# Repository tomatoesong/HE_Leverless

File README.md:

# HE_Leverless

# 🎮 Hall Effect Fighting Game Controller  

A custom-built **fighting game controller** featuring **Hall effect sensors** based on ESP32-S3 for ultra-durable, low latency performance. Designed for competitive play, modularity, and long-term reliability.  

---

## ✨ Features  

- 🕹 **Hall Effect Sensors** – no wear and tear from metal contact based switches 
- 🔧 **Modular Design** – easily replace buttons, just pull out an switch and snap in a new one
- ⚡ **Low Latency** – optimized input response at over 2000Hz polling with fully customizable actuation points for every switch!
- 🌐 **Web UI** - web based UI for customizing board on the go from anywhere without the need for connecting to a PC
- 💻 **Open Source Firmware** – customizable and community-driven  
- 🎨 **Custom Build** – unique layout and aesthetics  

---

## Custom PCB Layout  

| Front View |
|------------|
|  |

Created Using KiCad and custom library and footprints!

### ✅ PCB Features
- Digital and Analog ground plane seperation
- Low count BOM
- One sided for easy of assembly on hot plate or oven!

---

## Web-Based UI 

| Startup View | Selection | Save with Ease |
|------------|------------|------------|
|  |  |  |

Fully integrated and interactable WEB UI from an embedded board

### ✅ WEB-UI Features
- Hosts it's own Wifi you connect to
- Access the configurator from any browser at 192.168.10.1
- Individually switch values can be set with intuitive UI indicating what button you are adjusting
- 5 MICRON steps of adjustment for HIGH precision customization

---

## CAD Model  
<!--
| Front View | Inside View | 
|------------|-------------|
|  |  |

*(Replace the image paths with your actual files, e.g., `/assets/controller-front.png`)*  
-->
| Front View |
|------------|
|  |

| WireFrame View |
|------------|
|  |

Designed in Fusion360 with all components modeled for accuracy. 

---

## 🚀 Getting Started  

1. Clone this repo:  
   ```bash
   git clone https://github.com/your-username/your-controller-repo.git

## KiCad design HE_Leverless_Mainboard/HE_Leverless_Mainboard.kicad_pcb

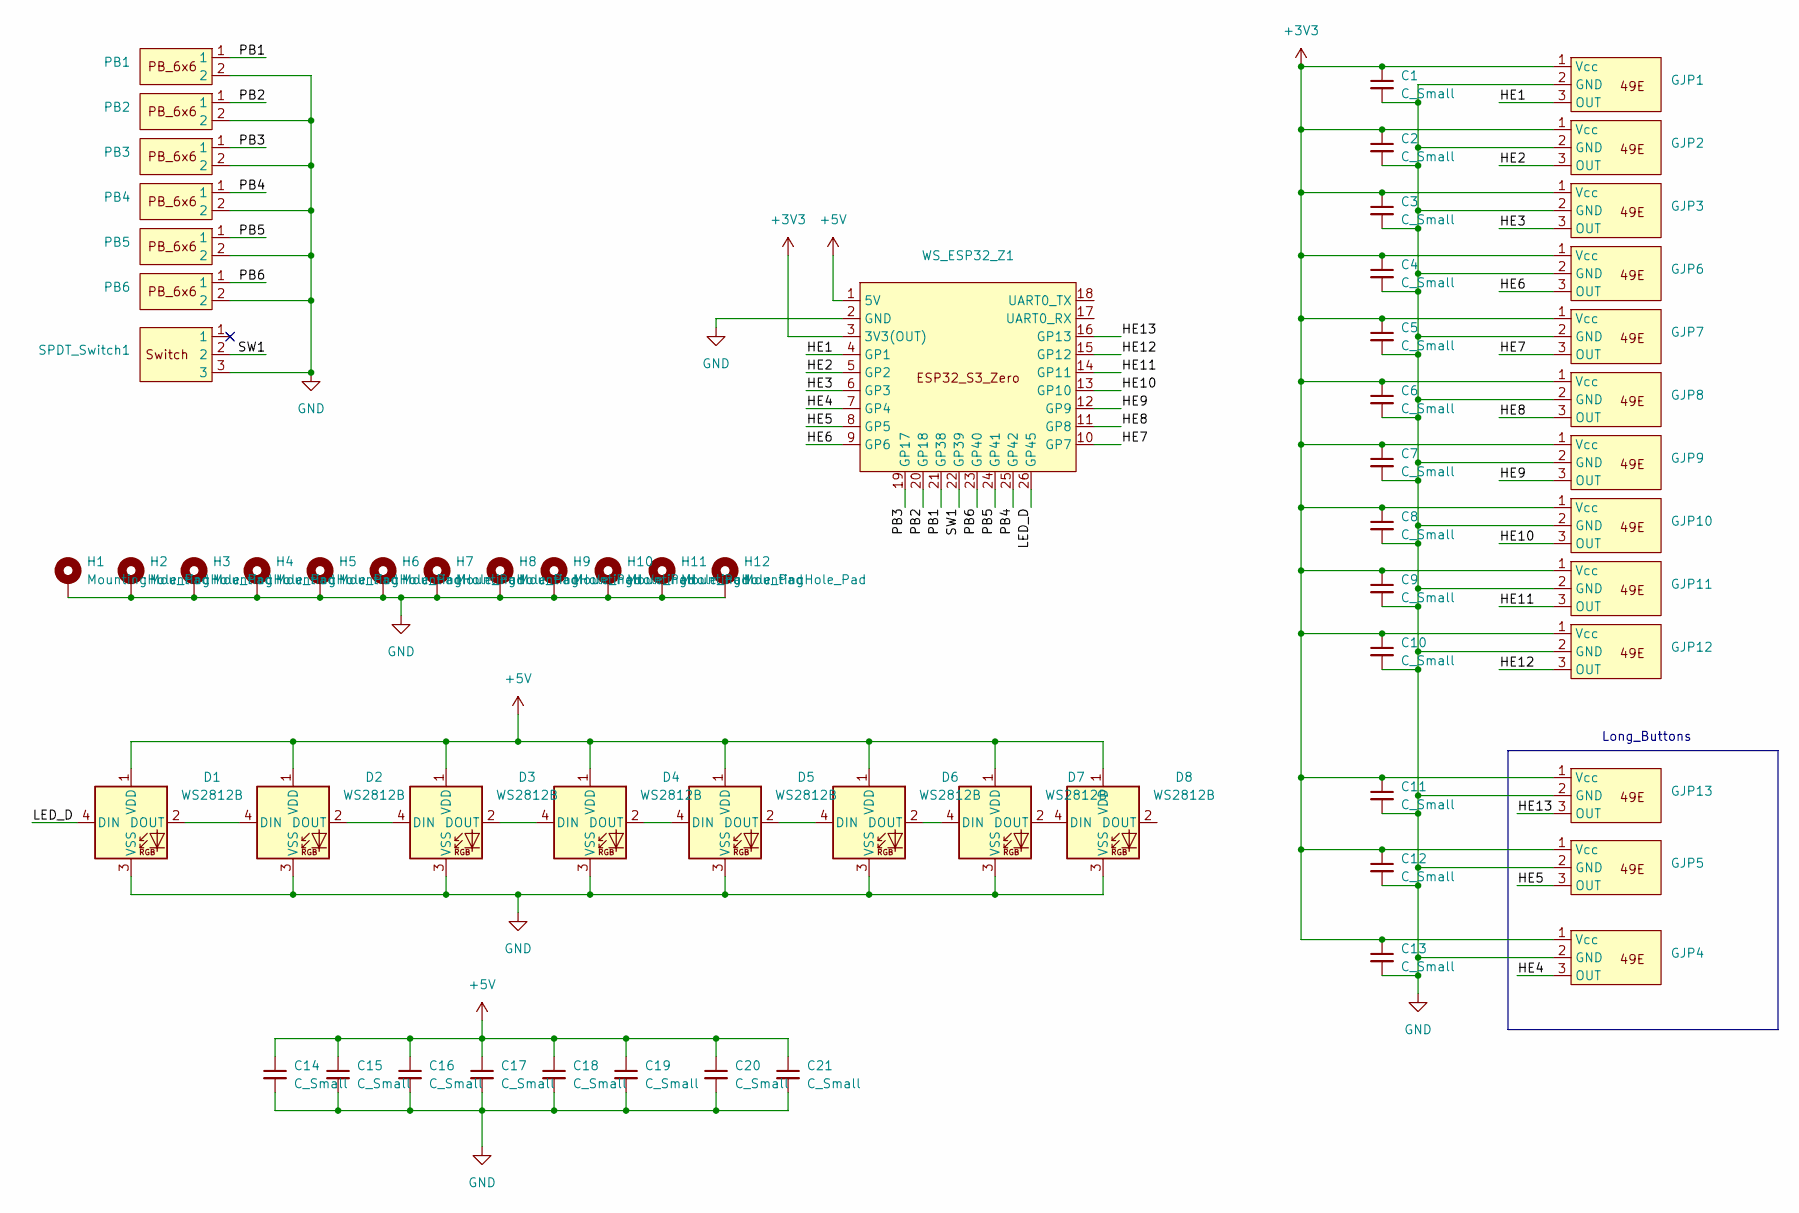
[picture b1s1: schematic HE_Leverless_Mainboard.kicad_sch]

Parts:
C1, C2, C3, C4, C5, C6, C7, C8, C9, C10, C11, C12, C13, C14, C15, C16, C17, C18, C19, C20, C21: C_Small; C_0805_2012Metric
D1, D2, D3, D4, D5, D6, D7, D8: WS2812B; LED_WS2812B_PLCC4_5.0x5.0mm_P3.2mm
GJP1, GJP2, GJP3, GJP6, GJP7, GJP8, GJP9, GJP10, GJP11, GJP12: Gateron_Jade_Pro
GJP4: Gateron_Jade_Pro_3
GJP5, GJP13: Gateron_Jade_Pro_2
H1, H2, H3, H4, H5, H6, H7, H8, H9, H10, H11, H12: MountingHole_Pad; MountingHole_3.2mm_M3_Pad
PB1, PB2, PB3, PB4, PB5, PB6: 6x6_PushButton
SPDT_Switch1: 1P2T_SPDT_Switch
WS_ESP32_Z1: WS_ESP32_S3_Zero

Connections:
+3V3: C1.1, C2.1, C3.1, C4.1, C5.1, C6.1, C7.1, C8.1, C9.1, C10.1, C11.1, C12.1, C13.1, GJP1.1 (Vcc), GJP2.1 (Vcc), GJP3.1 (Vcc), GJP4.1 (Vcc), GJP5.1 (Vcc), GJP6.1 (Vcc), GJP7.1 (Vcc), GJP8.1 (Vcc), GJP9.1 (Vcc), GJP10.1 (Vcc), GJP11.1 (Vcc), GJP12.1 (Vcc), GJP13.1 (Vcc), WS_ESP32_Z1.3 (3V3(OUT))
+5V: C14.1, C15.1, C16.1, C17.1, C18.1, C19.1, C20.1, C21.1, D1.1 (VDD), D2.1 (VDD), D3.1 (VDD), D4.1 (VDD), D5.1 (VDD), D6.1 (VDD), D7.1 (VDD), D8.1 (VDD), WS_ESP32_Z1.1 (5V)
/HE1: GJP1.3 (OUT), WS_ESP32_Z1.4 (GP1)
/HE2: GJP2.3 (OUT), WS_ESP32_Z1.5 (GP2)
/HE3: GJP3.3 (OUT), WS_ESP32_Z1.6 (GP3)
/HE4: GJP4.3 (OUT), WS_ESP32_Z1.7 (GP4)
/HE5: GJP5.3 (OUT), WS_ESP32_Z1.8 (GP5)
/HE6: GJP6.3 (OUT), WS_ESP32_Z1.9 (GP6)
/HE7: GJP7.3 (OUT), WS_ESP32_Z1.10 (GP7)
/HE8: GJP8.3 (OUT), WS_ESP32_Z1.11 (GP8)
/HE9: GJP9.3 (OUT), WS_ESP32_Z1.12 (GP9)
/HE10: GJP10.3 (OUT), WS_ESP32_Z1.13 (GP10)
/HE11: GJP11.3 (OUT), WS_ESP32_Z1.14 (GP11)
/HE12: GJP12.3 (OUT), WS_ESP32_Z1.15 (GP12)
/HE13: GJP13.3 (OUT), WS_ESP32_Z1.16 (GP13)
/LED_D: D1.4 (DIN), WS_ESP32_Z1.26 (GP45)
/PB1: PB1.1, WS_ESP32_Z1.21 (GP38)
/PB2: PB2.1, WS_ESP32_Z1.20 (GP18)
/PB3: PB3.1, WS_ESP32_Z1.19 (GP17)
/PB4: PB4.1, WS_ESP32_Z1.25 (GP42)
/PB5: PB5.1, WS_ESP32_Z1.24 (GP41)
/PB6: PB6.1, WS_ESP32_Z1.23 (GP40)
/SW1: SPDT_Switch1.2, WS_ESP32_Z1.22 (GP39)
GND: C1.2, C2.2, C3.2, C4.2, C5.2, C6.2, C7.2, C8.2, C9.2, C10.2, C11.2, C12.2, C13.2, C14.2, C15.2, C16.2, C17.2, C18.2, C19.2, C20.2, C21.2, D1.3 (VSS), D2.3 (VSS), D3.3 (VSS), D4.3 (VSS), D5.3 (VSS), D6.3 (VSS), D7.3 (VSS), D8.3 (VSS), GJP1.2 (GND), GJP2.2 (GND), GJP3.2 (GND), GJP4.2 (GND), GJP5.2 (GND), GJP6.2 (GND), GJP7.2 (GND), GJP8.2 (GND), GJP9.2 (GND), GJP10.2 (GND), GJP11.2 (GND), GJP12.2 (GND), GJP13.2 (GND), H1.1, H2.1, H3.1, H4.1, H5.1, H6.1, H7.1, H8.1, H9.1, H10.1, H11.1, H12.1, PB1.2, PB2.2, PB3.2, PB4.2, PB5.2, PB6.2, SPDT_Switch1.3, WS_ESP32_Z1.2 (GND)
unnamed: D1.2 (DOUT), D2.4 (DIN)
unnamed: D2.2 (DOUT), D3.4 (DIN)
unnamed: D3.2 (DOUT), D4.4 (DIN)
unnamed: D4.2 (DOUT), D5.4 (DIN)
unnamed: D5.2 (DOUT), D6.4 (DIN)
unnamed: D6.2 (DOUT), D7.4 (DIN)
unnamed: D7.2 (DOUT), D8.4 (DIN)

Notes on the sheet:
Long_Buttons

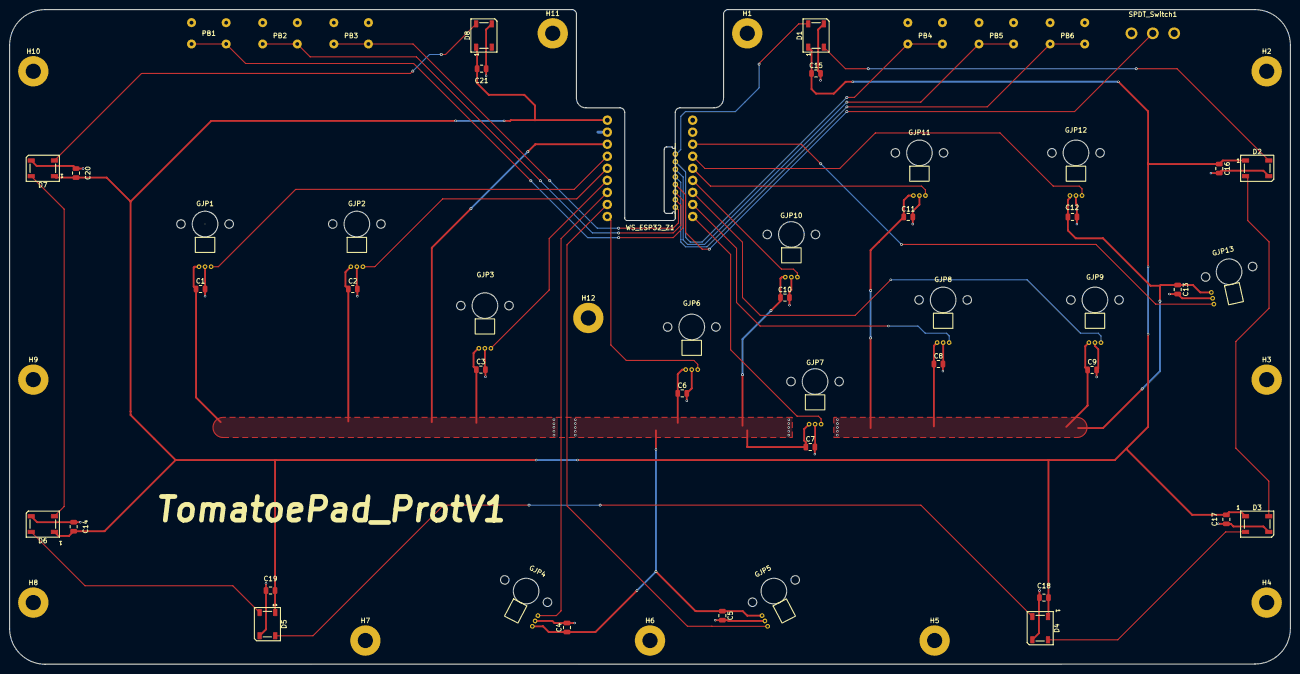
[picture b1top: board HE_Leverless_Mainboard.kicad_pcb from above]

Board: 2 copper layers, 270.0 x 138.0 mm, 62 parts (0 on the bottom side), 31 nets.

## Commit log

2025-06-07 MultiCore Progress
2025-06-12 Mass UPDATE
    - Massive organization overhaul
    - Added Rapid Trigger function
    - Calibration Protocol added
2025-06-30 default fill value
2025-07-04 Generic Gamepad functionality added
2025-07-12 AccessPoint hosting updates
2025-07-19 WebUI updated
    TO-DO: Add calibration sequence to WebUI
2025-09-25 Updated PCB
2025-09-25 file directory update
2025-09-25 Create LICENSE
2025-09-30 Added images
2025-09-30 additional UI images
